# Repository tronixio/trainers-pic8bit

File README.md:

# PIC 8-Bit Trainers Boards.

## Schematics.

- [**Nano** Trainer.](https://github.com/tronixio/trainers-pic8bit/blob/main/Kicad/nano/extras/schematic.pdf)
- [TODO - Micro Trainer.](https://github.com/tronixio/trainers-pic8bit/blob/main/Kicad/micro/extras/schematic.pdf)
- [**Mini** Trainer.](https://github.com/tronixio/trainers-pic8bit/blob/main/Kicad/mini/extras/schematic.pdf)
- [**PIC 8-Bit** Trainer.](https://github.com/tronixio/trainers-pic8bit/blob/main/Kicad/trainer/extras/schematic.pdf)

## Firmwares.

- [PIC 8-Bit NANO Trainer.](https://github.com/tronixio/trainers-pic8bit/tree/main/Firmwares#pic8-bit-nano-trainer)
- [PIC 8-Bit MINI Trainer.](https://github.com/tronixio/trainers-pic8bit/tree/main/Firmwares#pic8-bit-mini-trainer)
- [PIC 8-Bit Trainer.](https://github.com/tronixio/trainers-pic8bit/tree/main/Firmwares#pic8-bit-trainer)

## Hats & Modules.

- [Trainer Hats](https://github.com/tronixio/modules)
- [Trainer Modules (GPIO/UART/I2C/SPI)](https://github.com/tronixio/modules)

## NANO Trainer Top.

## NANO Trainer Bottom.

## MINI Trainer Top.

## MINI Trainer Bottom.

## PIC 8-Bit Trainer Top.

## PIC 8-Bit Trainer Bottom.

## Notes.

- DRAFT : Prototype OK, last check schematic, PCB & code can be modify.
- TODO : Work in progress, prototype was not good, hardware, PCB and code can be rework.

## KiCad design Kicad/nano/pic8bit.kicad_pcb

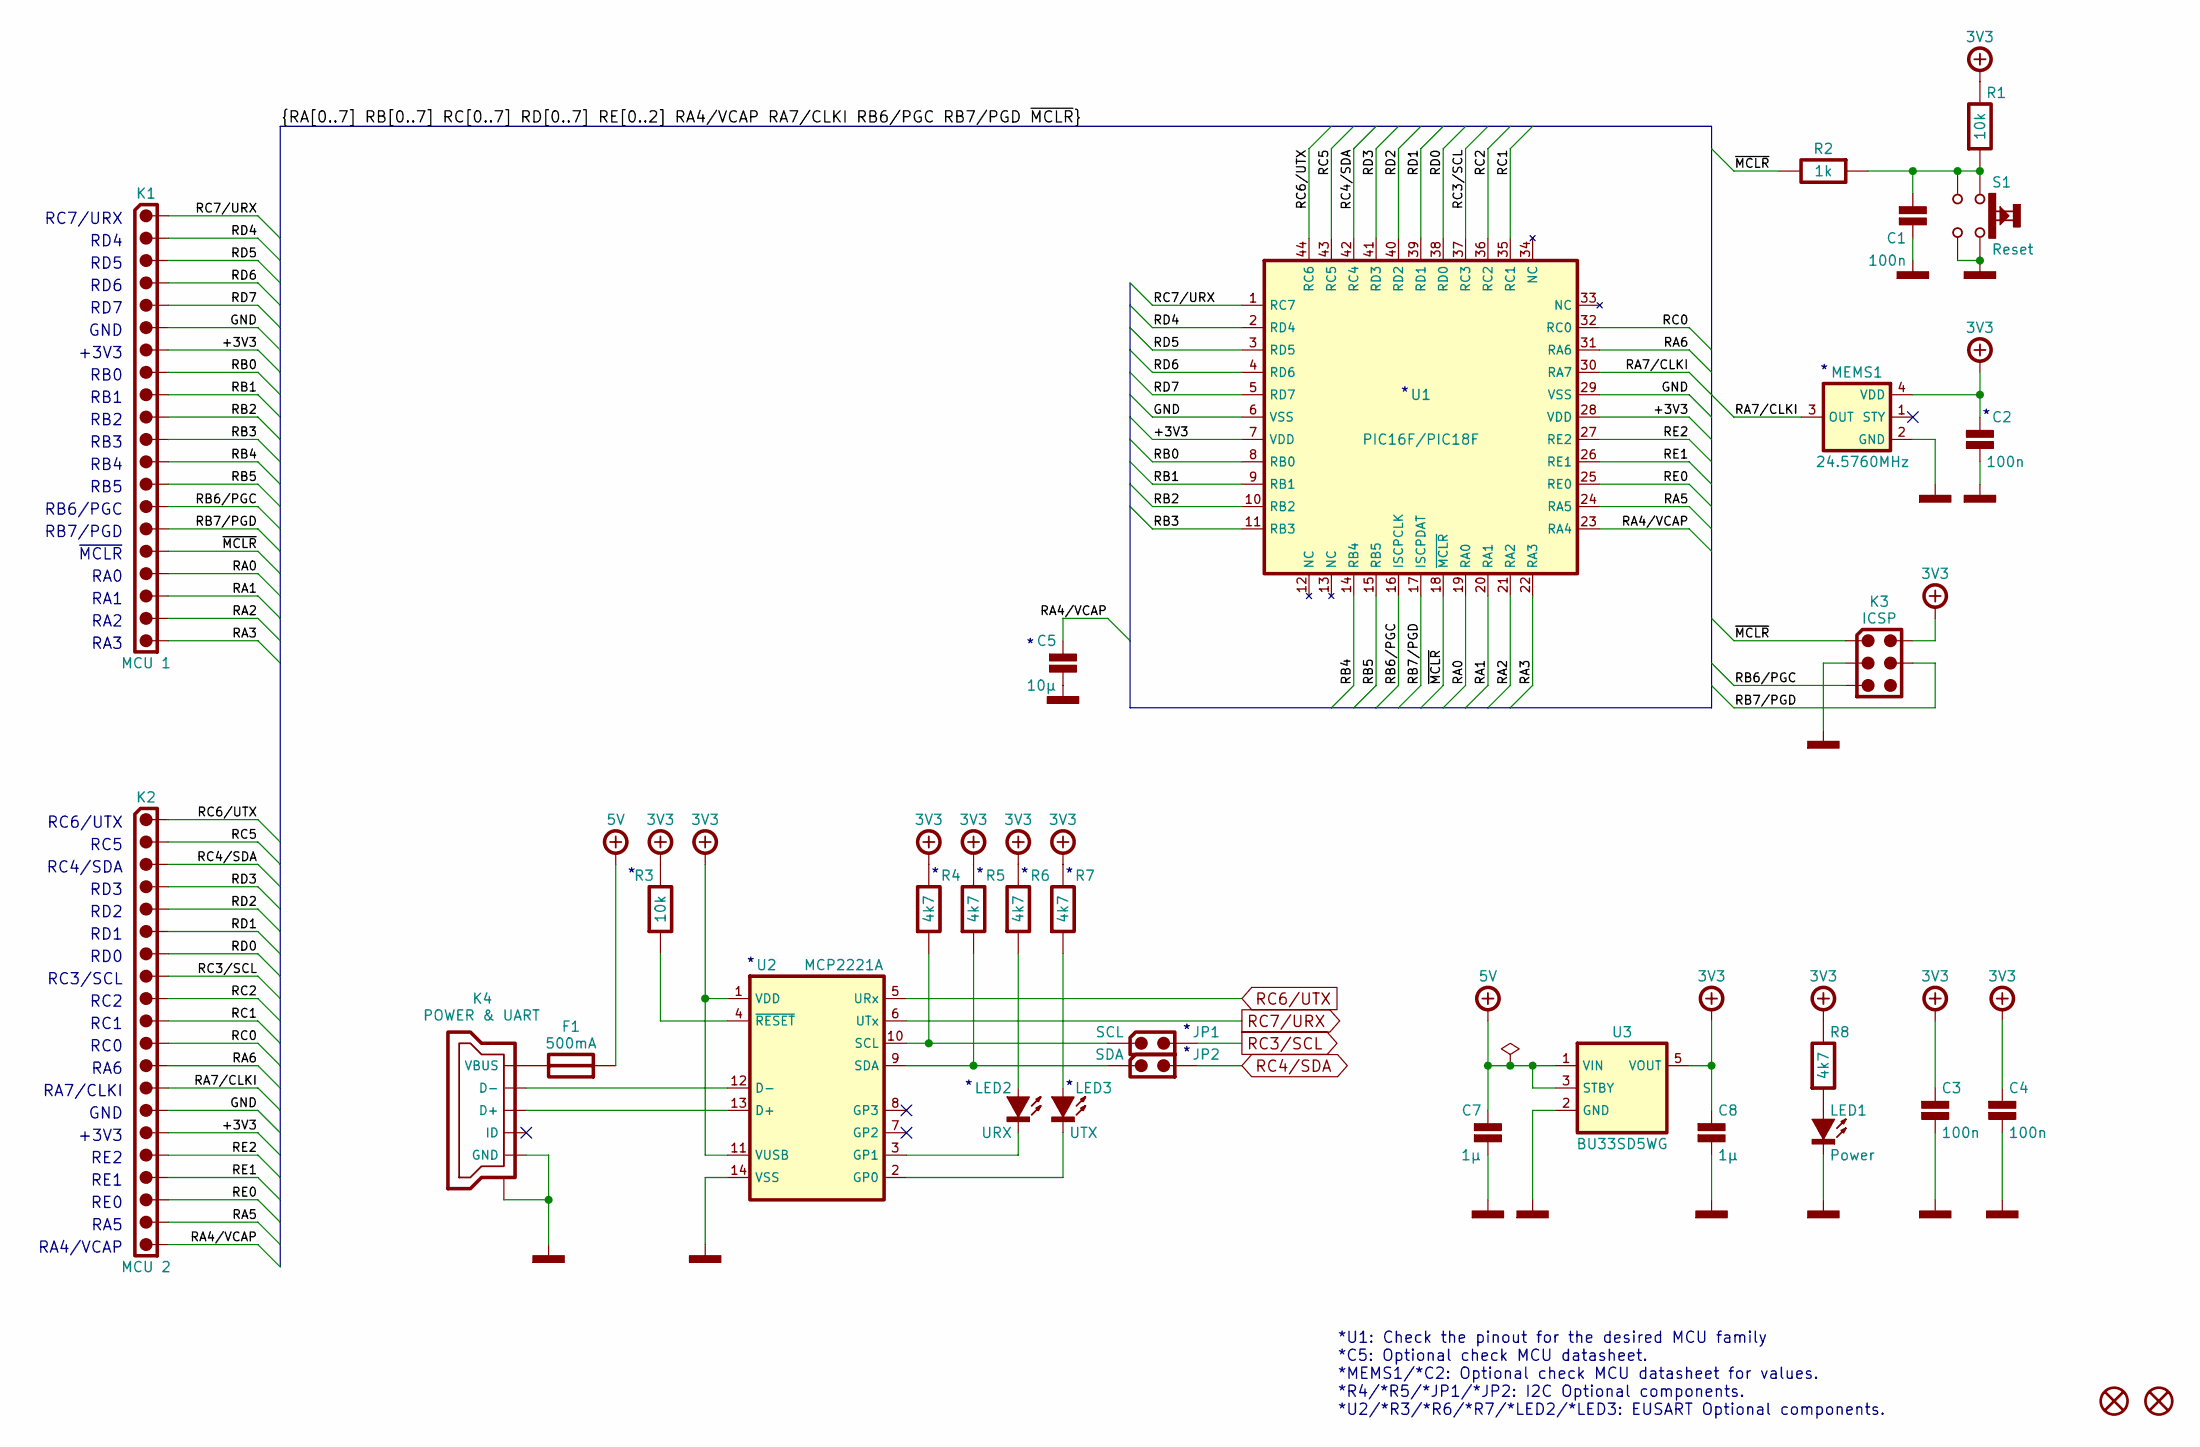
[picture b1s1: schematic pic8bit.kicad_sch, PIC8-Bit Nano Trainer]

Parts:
C1, C2, C3, C4: 100n; CAPACITOR-SMD-0805; Voltage 50V; Tolerance 5%; Mouser 80-C0805C104J5
C5: 10µ; CAPACITOR-SMD-0805; Voltage 25V; Tolerance 10%; Mouser 81-GRM21BZ71E106
C7, C8: 1µ; CAPACITOR-SMD-0805; Voltage 50V; Tolerance 10%; Mouser 187-CL21B105KBFNNNE
F1: 500mA; FUSE-SMD-0805; Mouser 652-MF-PSMF050X-2
H1, H2: HARWIN-JUMPER-0200-03MM-BLACK; HARWIN-M22-190-19X; Mouser 855-M22-19000
JP1: SCL; HARWIN-M22-25102xx; Mouser 855-M22-25102
JP2: SDA; HARWIN-M22-25102xx; Mouser 855-M22-25102
K1: MCU 1; SAMTEC-TSW-120-22-T-S; Mouser 200-TSW12022TS
K2: MCU 2; SAMTEC-TSW-120-22-T-S; Mouser 200-TSW12022TS
K3: ICSP; HARWIN-M20-998034x; Mouser 855-M20-998034
K4: POWER & UART; USB-TYPE-B-MICRO-TH; Mouser 649-10118193-0001LF
LED1: Power; LED-SMD-0805; Mouser 604-APT2012LVBCD
LED2: URX; LED-SMD-0805; Mouser 604-APT2012LVBCD
LED3: UTX; LED-SMD-0805; Mouser 604-APT2012LVBCD
MEMS1: 24.5760MHz; CDFN-3225; Mouser 998-1001CI2-024.5760
R1, R3: 10k; RESISTOR-SMD-0805; Tolerance 5%; Mouser 660-RK73B2ATTDD103J
R2: 1k; RESISTOR-SMD-0805; Tolerance 5%; Mouser 660-RK73B2ATTDD102J
R4, R5, R6, R7, R8: 4k7; RESISTOR-SMD-0805; Tolerance 5%; Mouser 660-RK73B2ATTDD472J
S1: Reset; ALPS-SKRPAC; Mouser 688-SKRPACE010
U1: PIC16F/PIC18F; TQFP-44; Mouser 579-PIC16F1779-I/PT
U2: MCP2221A; TSSOP-14; Mouser 579-MCP2221A-I/ST
U3: BU33SD5WG; SOT-23-5; Mouser 755-BU33SD5WG-TR

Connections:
+3V3: C2.1, C3.1, C4.1, C8.1, K1.7, K2.15, K3.2 (VCC), MEMS1.4 (VDD), R1.1, R3.1, R4.1, R5.1, R6.1, R7.1, R8.1, U1.7 (VDD), U1.28 (VDD), U2.1 (VDD), U2.11 (VUSB), U3.5 (VOUT)
/RA0: K1.17, U1.19 (RA0)
/RA1: K1.18, U1.20 (RA1)
/RA2: K1.19, U1.21 (RA2)
/RA3: K1.20, U1.22 (RA3)
/RA4/VCAP: C5.1, K2.20, U1.23 (RA4)
/RA5: K2.19, U1.24 (RA5)
/RA6: K2.12, U1.31 (RA6)
/RA7/CLKI: K2.13, MEMS1.3 (OUT), U1.30 (RA7)
/RB0: K1.8, U1.8 (RB0)
/RB1: K1.9, U1.9 (RB1)
/RB2: K1.10, U1.10 (RB2)
/RB3: K1.11, U1.11 (RB3)
/RB4: K1.12, U1.14 (RB4)
/RB5: K1.13, U1.15 (RB5)
/RB6/PGC: K1.14, K3.5 (ICSPCLK), U1.16 (ISCPCLK)
/RB7/PGD: K1.15, K3.4 (ICSPDAT), U1.17 (ISCPDAT)
/RC0: K2.11, U1.32 (RC0)
/RC1: K2.10, U1.35 (RC1)
/RC2: K2.9, U1.36 (RC2)
/RC5: K2.2, U1.43 (RC5)
/RD0: K2.7, U1.38 (RD0)
/RD1: K2.6, U1.39 (RD1)
/RD2: K2.5, U1.40 (RD2)
/RD3: K2.4, U1.41 (RD3)
/RD4: K1.2, U1.2 (RD4)
/RD5: K1.3, U1.3 (RD5)
/RD6: K1.4, U1.4 (RD6)
/RD7: K1.5, U1.5 (RD7)
/RE0: K2.18, U1.25 (RE0)
/RE1: K2.17, U1.26 (RE1)
/RE2: K2.16, U1.27 (RE2)
/~MCLR: K1.16, K3.1 (~MCLR), R2.1, U1.18 (~MCLR)
GND: C1.2, C2.2, C3.2, C4.2, C5.2, C7.2, C8.2, K1.6, K2.14, K3.3 (GND), K4.5 (GND), K4.SH (SHIELD), LED1.1 (C), MEMS1.2 (GND), S1.3, S1.4, U1.6 (VSS), U1.29 (VSS), U2.14 (VSS), U3.2 (GND)
unnamed: C1.1, R1.2, R2.2, S1.1, S1.2
unnamed: K4.3 (D+), U2.13 (D+)
unnamed: K4.2 (D-), U2.12 (D-)
unnamed: F1.1, K4.1 (VBUS)
unnamed: LED1.2 (A), R8.2
unnamed: LED2.2 (A), R6.2
unnamed: LED2.1 (C), U2.3 (GP1)
unnamed: LED3.2 (A), R7.2
unnamed: LED3.1 (C), U2.2 (GP0)
unnamed: JP1.1, R4.2, U2.10 (SCL)
unnamed: JP2.1, R5.2, U2.9 (SDA)
unnamed: R3.2, U2.4 (~RESET)
POWER-+5V: C7.1, F1.2, U3.1 (VIN), U3.3 (STBY)
RC3/SCL: JP1.2, K2.8, U1.37 (RC3)
RC4/SDA: JP2.2, K2.3, U1.42 (RC4)
RC6/UTX: K2.1, U1.44 (RC6), U2.5 (URx)
RC7/URX: K1.1, U1.1 (RC7), U2.6 (UTx)

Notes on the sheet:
RD7
RA7/CLKI
RB0
RD5
RC6/UTX
GND
RB4
RA4/VCAP
RB1
RE0
RC3/SCL
~{MCLR}
RB2
+3V3
RE1
RB5
RA6
RD1
RD3
RD6
RB3
RA3
*U1: Check the pinout for the desired MCU family *C5: Optional check MCU datasheet. *MEMS1/*C2: Optional check MCU datasheet for values. *R4/*R5/*JP1/*JP2: I2C Optional components. *U2/*R3/*R6/*R7/*LED2/*LED3: EUSART Optional components.
RE2
RA1
RB7/PGD
RA2
RC5
RC0
RC4/SDA
RA0
RA5
RB6/PGC
RD2
RD0
RC2
RC7/URX
RC1
RD4

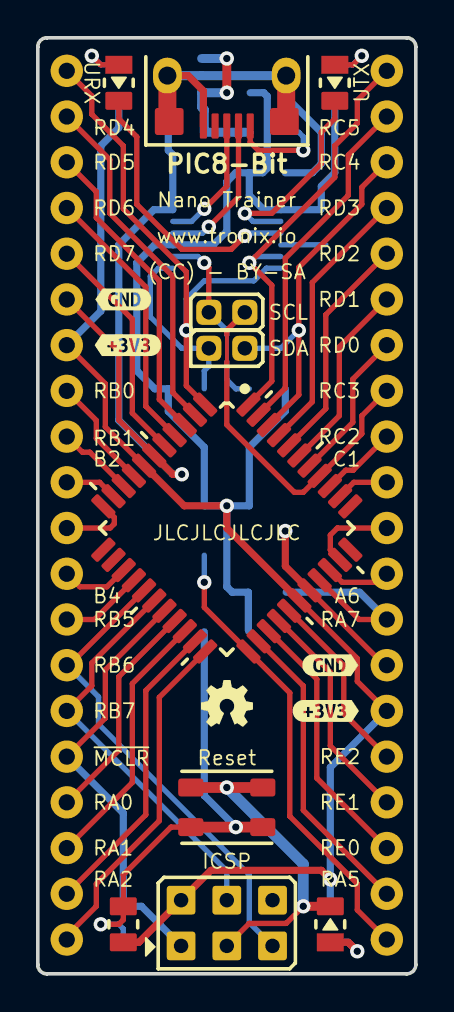
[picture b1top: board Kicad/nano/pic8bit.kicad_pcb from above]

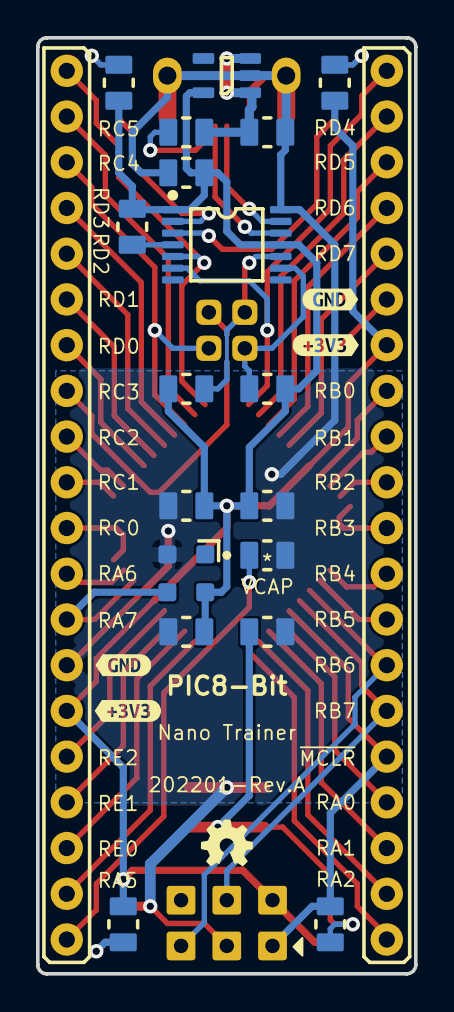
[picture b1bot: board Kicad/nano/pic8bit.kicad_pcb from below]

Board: 2 copper layers, 21.0 x 52.0 mm, 42 parts (25 on the bottom side), 51 nets.

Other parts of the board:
GB: LOGO; OSHW-3MM
GT: LOGO; OSHW-3MM
kibuzzard-65F5BE0B: G***; kibuzzard-65F5BE0B
kibuzzard-65F5BE2C: G***; kibuzzard-65F5BE2C
kibuzzard-65F5BE3D: G***; kibuzzard-65F5BE3D
kibuzzard-65F5BE5D: G***; kibuzzard-65F5BE5D
kibuzzard-65F5BE6D: G***; kibuzzard-65F5BE6D
kibuzzard-65F5BE7D: G***; kibuzzard-65F5BE7D
kibuzzard-65F5BE8C: G***; kibuzzard-65F5BE8C
kibuzzard-65F5BE49: G***; kibuzzard-65F5BE49

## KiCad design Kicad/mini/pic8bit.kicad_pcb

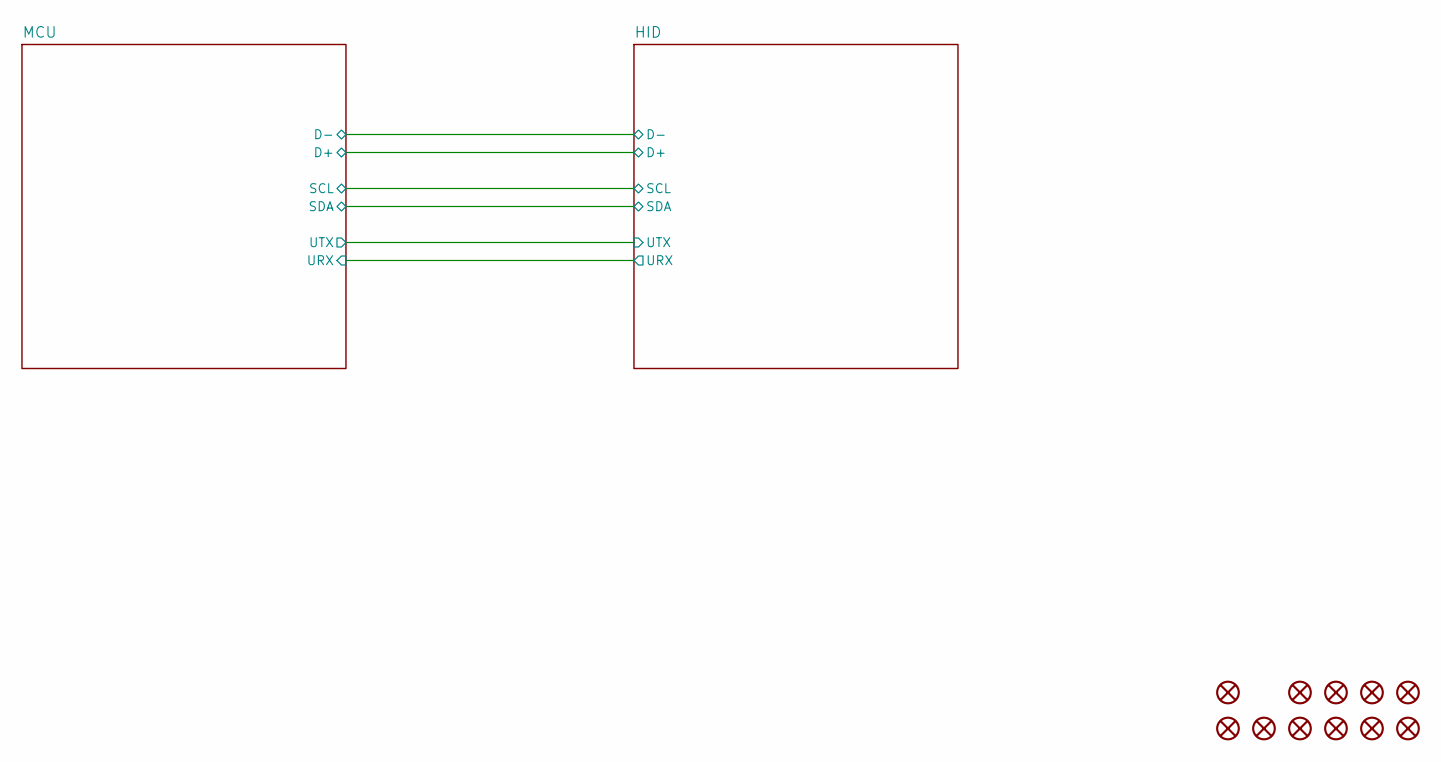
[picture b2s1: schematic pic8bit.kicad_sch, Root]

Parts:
H101, H102, H103, H104: KEYSTONE-9055; Mouser 534-9055
JP101, JP102, JP103, JP104, JP105, JP106: HARWIN-JUMPER-0254-06MM-BLACK; HARWIN-M20-7580-7583; Mouser 855-M7582
K101: PE-450-4X6X-BLACK; PE-450-4X6X; Mouser 450-476

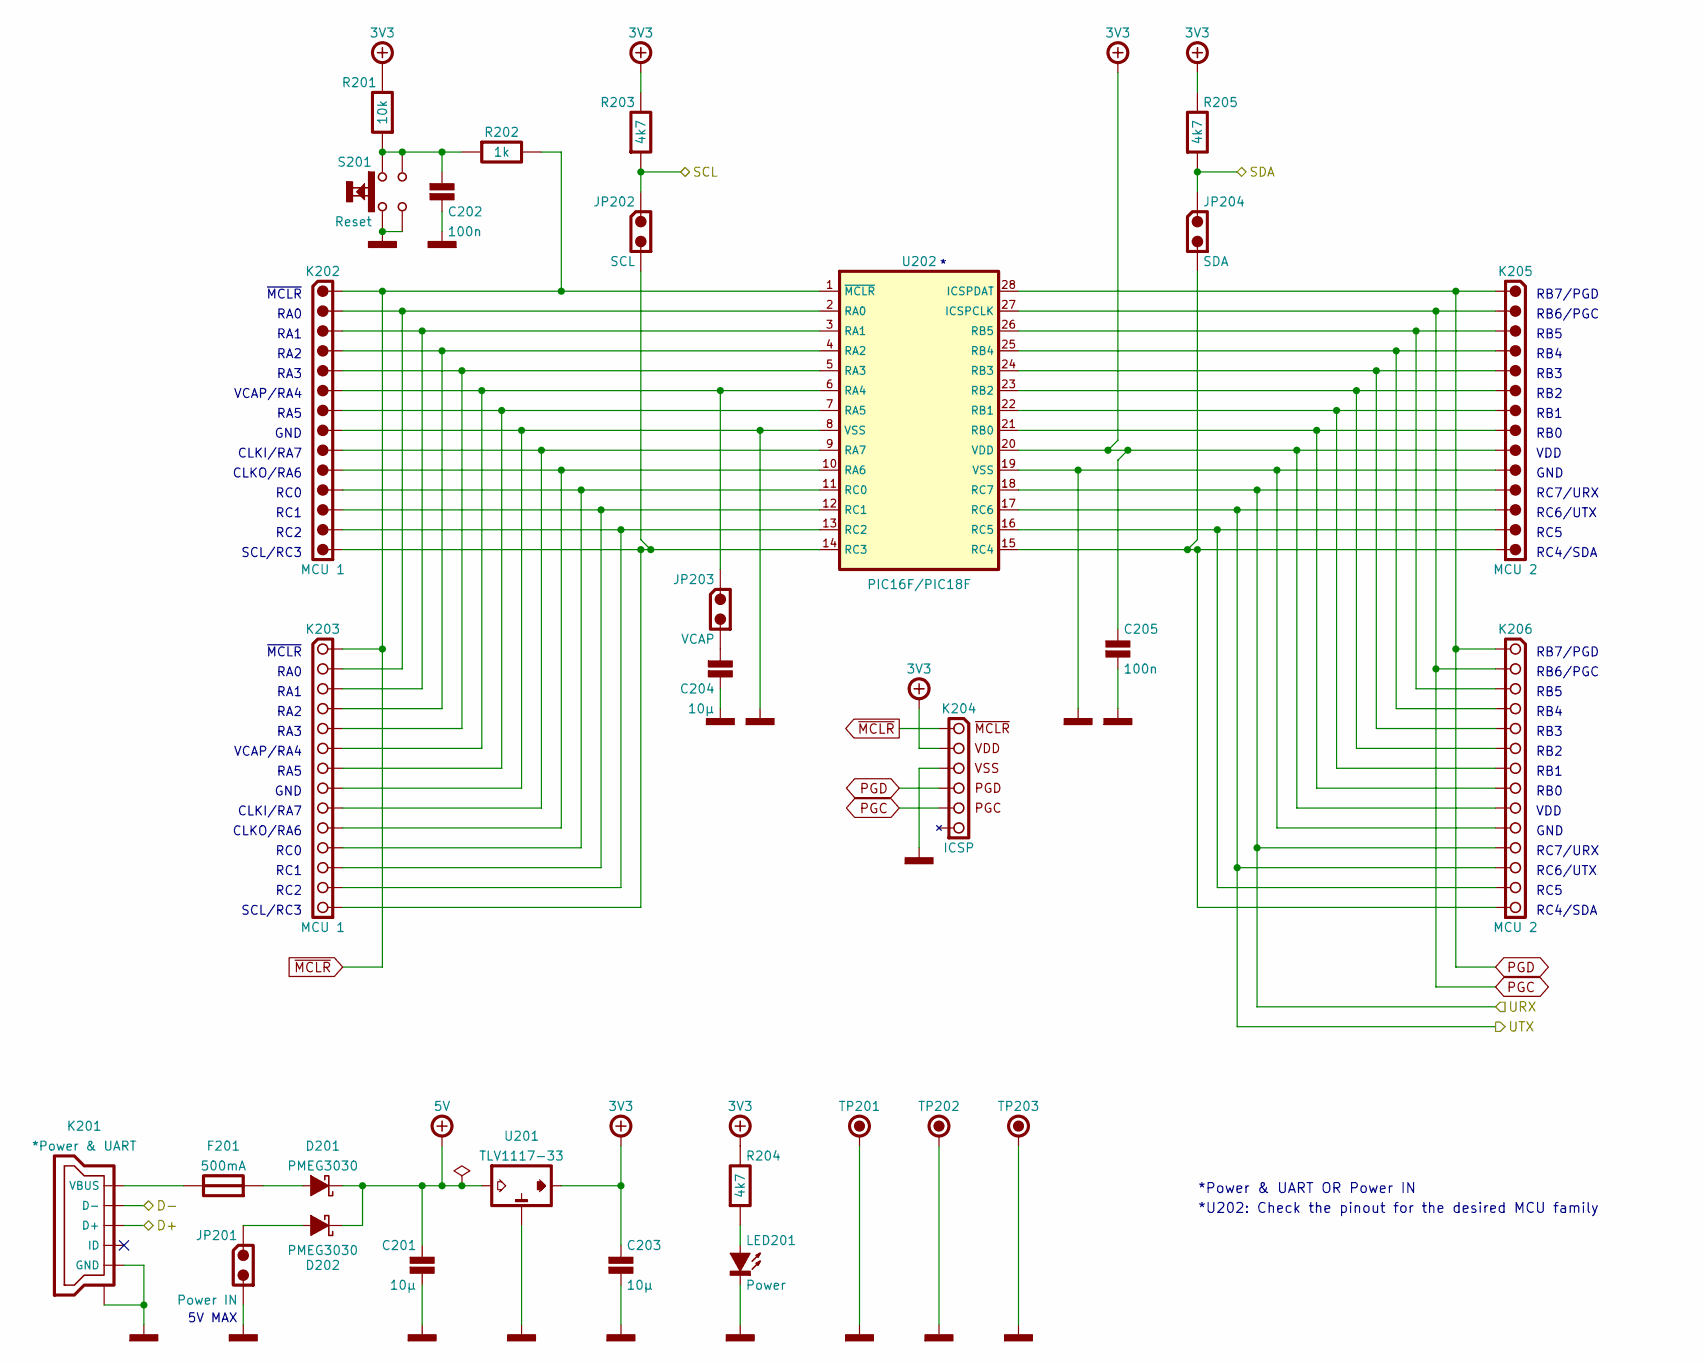
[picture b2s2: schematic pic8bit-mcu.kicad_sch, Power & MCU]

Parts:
C201, C203, C204: 10µ; CAPACITOR-SMD-1206; Tolerance 5%; Voltage 25V; Mouser 80-C1206C106J3R
C202, C205: 100n; CAPACITOR-SMD-1206; Voltage 50V; Tolerance 5%; Mouser 80-C1206C104J5R
D201, D202: PMEG3030; SOD-128; Part Marking A5; Mouser 771-PMEG3030EP115
F201: 500mA; FUSE-SMD-1206; Mouser 652-MF-NSMF050-2
JP201: Power IN; HARWIN-M20-999024x; Mouser 855-M20-999024
JP202: SCL; HARWIN-M20-999024x; Mouser 855-M20-999024
JP203: VCAP; HARWIN-M20-999024x; Mouser 855-M20-999024
JP204: SDA; HARWIN-M20-999024x; Mouser 855-M20-999024
K201: *Power & UART; USB-TYPE-B-MICRO-TH; Mouser 649-10118193-0001LF
K202: MCU 1; HARWIN-M20-999144x; Mouser 855-M20-999144
K203: MCU 1; HARWIN-M20-782144x; Mouser 855-M20-782144
K204: ICSP; SAMTEC-SSW-106-02-T-S-RA; Mouser 200-SSW10602TSRA
K205: MCU 2; HARWIN-M20-999144x; Mouser 855-M20-999144
K206: MCU 2; HARWIN-M20-782144x; Mouser 855-M20-782144
LED201: Power; LED-SMD-1206; Mouser 604-APT3216LVBCD
R201: 10k; RESISTOR-SMD-1206; Tolerance 5%; Mouser 660-RK73B2BTTDD103J
R202: 1k; RESISTOR-SMD-1206; Tolerance 5%; Mouser 660-RK73B2BTTDD102J
R203, R204, R205: 4k7; RESISTOR-SMD-1206; Tolerance 5%; Mouser 660-RK73B2BTTDD472J
S201: Reset; ALPS-SKRPAC; Mouser 688-SKRPACE010
TP201, TP202: KEYSTONE-5006; Mouser 534-5006
TP203: KEYSTONE-2000-3; Mouser 534-2000-3
U201: TLV1117-33; SOT-223-3-TABPIN2; Mouser 595-TLV1117-33CDC
U202: PIC16F/PIC18F; DIP-28-W762; Mouser 579-PIC16F1778-I/SP

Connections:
/HID/D+: K201.3 (D+); also elsewhere on the board
/HID/D-: K201.2 (D-); also elsewhere on the board
/HID/SCL: JP202.1, R203.2; also elsewhere on the board
/HID/SDA: JP204.1, R205.2; also elsewhere on the board
/HID/URX: K205.11, K206.11, U202.18 (RC7); also elsewhere on the board
/HID/UTX: K205.12, K206.12, U202.17 (RC6); also elsewhere on the board
unnamed: C202.1, R201.2, R202.2, S201.1, S201.2
unnamed: C204.1, JP203.2
unnamed: D201.2 (A), F201.2
unnamed: D202.2 (A), JP201.1
unnamed: F201.1, K201.1 (VBUS)
unnamed: K202.2, K203.2, U202.2 (RA0)
unnamed: K202.3, K203.3, U202.3 (RA1)
unnamed: K202.4, K203.4, U202.4 (RA2)
unnamed: K202.5, K203.5, U202.5 (RA3)
unnamed: JP203.1, K202.6, K203.6, U202.6 (RA4)
unnamed: K202.7, K203.7, U202.7 (RA5)
unnamed: K202.9, K203.9, U202.9 (RA7)
unnamed: K202.10, K203.10, U202.10 (RA6)
unnamed: K202.11, K203.11, U202.11 (RC0)
unnamed: K202.12, K203.12, U202.12 (RC1)
unnamed: K202.13, K203.13, U202.13 (RC2)
unnamed: JP202.2, K202.14, K203.14, U202.14 (RC3)
unnamed: K205.3, K206.3, U202.26 (RB5)
unnamed: K205.4, K206.4, U202.25 (RB4)
unnamed: K205.5, K206.5, U202.24 (RB3)
unnamed: K205.6, K206.6, U202.23 (RB2)
unnamed: K205.7, K206.7, U202.22 (RB1)
unnamed: K205.8, K206.8, U202.21 (RB0)
unnamed: K205.13, K206.13, U202.16 (RC5)
unnamed: JP204.2, K205.14, K206.14, U202.15 (RC4)
unnamed: LED201.2 (A), R204.2
PGC: K204.2 (PGC), K205.2, K206.2, U202.27 (ICSPCLK)
PGD: K204.3 (PGD), K205.1, K206.1, U202.28 (ICSPDAT)
POWER-+3V3: C203.1, C205.1, K204.5 (VCC), K205.9, K206.9, R201.1, R203.1, R204.1, R205.1, U201.2 (VOUT), U202.20 (VDD); also elsewhere on the board
POWER-+5V: C201.1, D201.1 (C), D202.1 (C), U201.3 (VIN); also elsewhere on the board
POWER-GND: C201.2, C202.2, C203.2, C204.2, C205.2, JP201.2, K201.5 (GND), K201.SH (SHIELD), K202.8, K203.8, K204.4 (GND), K205.10, K206.10, LED201.1 (C), S201.3, S201.4, TP201.1, TP202.1, TP203.1, U201.1 (GND), U202.8 (VSS), U202.19 (VSS); also elsewhere on the board
~MCLR: K202.1, K203.1, K204.6 (~MCLR), R202.1, U202.1 (~MCLR)

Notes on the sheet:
RC6/UTX
*U202: Check the pinout for the desired MCU family
GND
RB3
~{MCLR}
VCAP/RA4
*Power & UART OR Power IN
CLKI/RA7
RC5
RB6/PGC
RA2
VDD
RA3
RC0
RA0
RC1
RB7/PGD
RB5
RB2
RA5
RB1
RA1
CLKO/RA6
SCL/RC3
RB4
RC7/URX
RB0
5V MAX
RC4/SDA
RC2

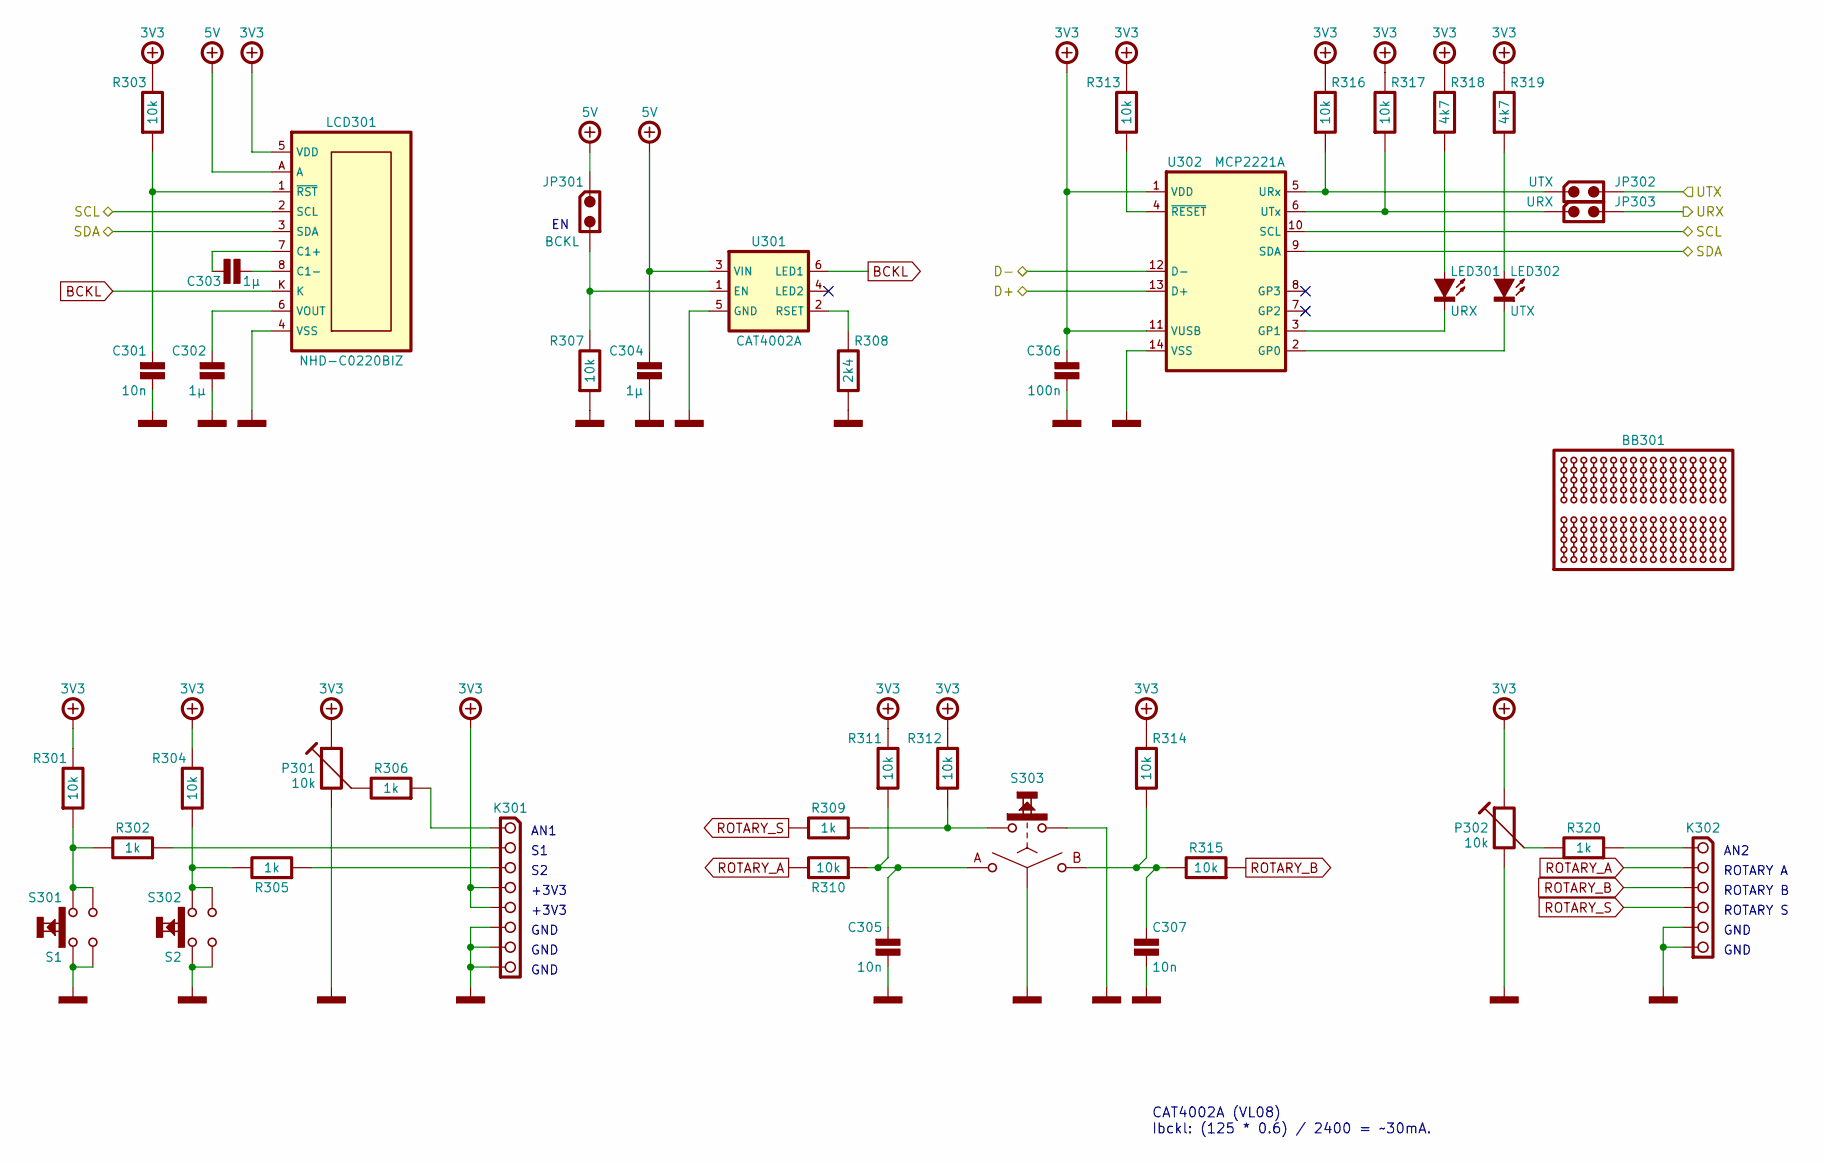
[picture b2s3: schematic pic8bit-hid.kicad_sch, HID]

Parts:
BB301: BREADBOARD-170; Mouser 854-BB170
C301, C305, C307: 10n; CAPACITOR-SMD-1206; Voltage 100V; Tolerance 5%; Mouser 80-C1206C103J1R
C302, C303, C304: 1µ; CAPACITOR-SMD-1206; Voltage 16V; Tolerance 10%; Mouser 80-C1206C105K4R
C306: 100n; CAPACITOR-SMD-1206; Voltage 50V; Tolerance 5%; Mouser 80-C1206C104J5R
JP301: BCKL; HARWIN-M20-999024x; Mouser 855-M20-999024
JP302: UTX; HARWIN-M20-999024x; Mouser 855-M20-999024
JP303: URX; HARWIN-M20-999024x; Mouser 855-M20-999024
K301: HARWIN-254-F-1X08-VERTICAL; HARWIN-M20-782084x; Mouser 855-M20-782084
K302: HARWIN-254-F-1X06-VERTICAL; HARWIN-M20-782064x; Mouser 855-M20-782064
LCD301: NHD-C0220BIZ; Mouser 763-C0220BIZ-FSW-FBW
LED301: URX; LED-SMD-1206; Mouser 604-APT3216LVBCD
LED302: UTX; LED-SMD-1206; Mouser 604-APT3216LVBCD
P301, P302: 10k; PIHER-PT10MV; Tolerance 20%; Mouser 531-PT10MV-10K
R301, R303, R304, R307, R310, R311, R312, R313, R314, R315, R316, R317: 10k; RESISTOR-SMD-1206; Tolerance 5%; Mouser 660-RK73B2BTTDD103J
R302, R305, R306, R309, R320: 1k; RESISTOR-SMD-1206; Tolerance 5%; Mouser 660-RK73B2BTTDD102J
R308: 2k4; RESISTOR-SMD-1206; Tolerance 5%; Mouser 660-RK73B2BTTDD242J
R318, R319: 4k7; RESISTOR-SMD-1206; Tolerance 5%; Mouser 660-RK73B2BTTDD472J
S301: S1; CK-KSA-TH; Mouser 611-KSA0M911LFT
S302: S2; CK-KSA-TH; Mouser 611-KSA0M911LFT
S303: BOURNS-PEC12R-24DENTS-SWITCH; BOURNS-PEC12R-SWITCH; Mouser 652-PEC12R-4215F-S24
U301: CAT4002A; SC-70-6; Mouser 863-CAT4002ASD-GT3
U302: MCP2221A; SOIC-14; Mouser 579-MCP2221A-I/SL

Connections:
/HID/D+: U302.13 (D+); also elsewhere on the board
/HID/D-: U302.12 (D-); also elsewhere on the board
/HID/SCL: LCD301.2 (SCL), U302.10 (SCL); also elsewhere on the board
/HID/SDA: LCD301.3 (SDA), U302.9 (SDA); also elsewhere on the board
/HID/URX: JP303.2; also elsewhere on the board
/HID/UTX: JP302.2; also elsewhere on the board
BCKL: LCD301.K, U301.6 (LED1)
unnamed: K301.1, R306.2
unnamed: K301.2, R302.2
unnamed: K301.3, R305.2
unnamed: K302.1, R320.2
unnamed: C303.1, LCD301.7 (C1+)
unnamed: C303.2, LCD301.8 (C1-)
unnamed: C302.1, LCD301.6 (VOUT)
unnamed: C301.1, LCD301.1 (~RST), R303.2
unnamed: LED301.2 (A), R318.2
unnamed: LED301.1 (C), U302.3 (GP1)
unnamed: LED302.2 (A), R319.2
unnamed: LED302.1 (C), U302.2 (GP0)
unnamed: P301.2, R306.1
unnamed: P302.2, R320.1
unnamed: R301.2, R302.1, S301.3, S301.4
unnamed: R304.2, R305.1, S302.3, S302.4
unnamed: R309.2, R312.2, S303.5
unnamed: C305.1, R310.2, R311.2, S303.1 (A)
unnamed: C307.1, R314.2, R315.1, S303.3 (B)
unnamed: JP301.2, R307.1, U301.1 (EN)
unnamed: R308.1, U301.2 (RSET)
unnamed: JP302.1, R316.2, U302.5 (URx)
unnamed: JP303.1, R317.2, U302.6 (UTx)
unnamed: R313.2, U302.4 (~RESET)
POWER-+3V3: C306.1, K301.4, K301.5, LCD301.5 (VDD), P301.3, P302.3, R301.1, R303.1, R304.1, R311.1, R312.1, R313.1, R314.1, R316.1, R317.1, R318.1, R319.1, U302.1 (VDD), U302.11 (VUSB); also elsewhere on the board
POWER-+5V: C304.1, JP301.1, LCD301.A, U301.3 (VIN); also elsewhere on the board
POWER-GND: C301.2, C302.2, C304.2, C305.2, C306.2, C307.2, K301.6, K301.7, K301.8, K302.5, K302.6, LCD301.4 (VSS), P301.1, P302.1, R307.2, R308.2, S301.1, S301.2, S302.1, S302.2, S303.2 (C), S303.4, U301.5 (GND), U302.14 (VSS); also elsewhere on the board
ROTARY_A: K302.2, R310.1
ROTARY_B: K302.3, R315.2
ROTARY_S: K302.4, R309.1

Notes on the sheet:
AN1
GND
ROTARY A
ROTARY B
AN2
+3V3
CAT4002A (VL08) Ibckl: (125 * 0.6) / 2400 = ~30mA.
ROTARY S

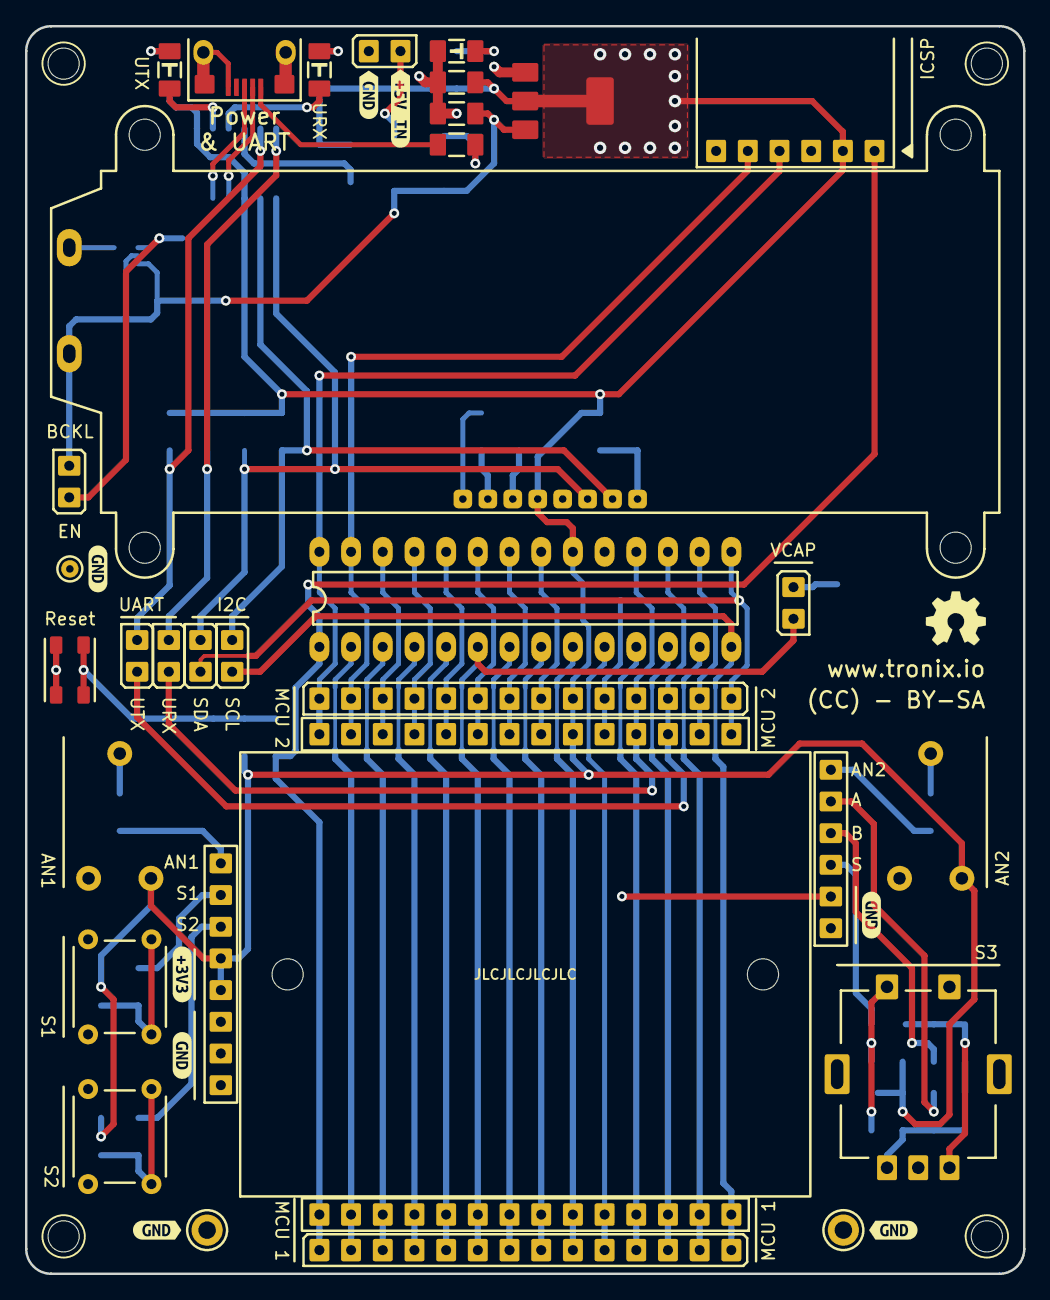
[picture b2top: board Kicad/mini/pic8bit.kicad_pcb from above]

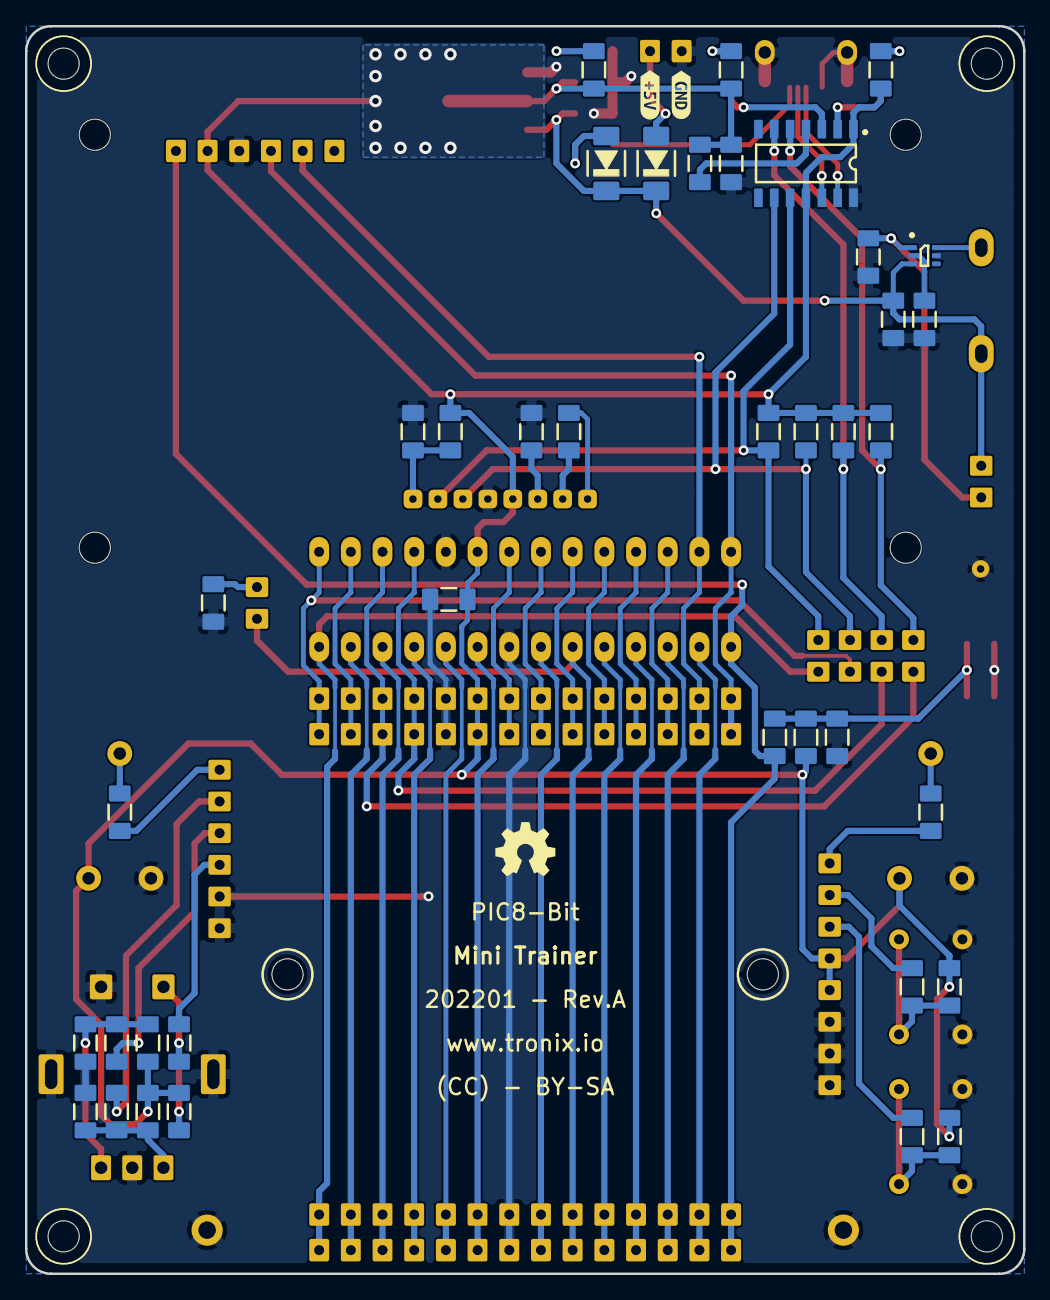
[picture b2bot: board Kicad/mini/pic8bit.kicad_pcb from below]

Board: 2 copper layers, 80.0 x 100.0 mm, 94 parts (41 on the bottom side), 66 nets.

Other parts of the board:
kibuzzard-65F5FBF2: G***; kibuzzard-65F5FBF2
kibuzzard-65F5FC1C: G***; kibuzzard-65F5FC1C
kibuzzard-65F5FC3B: G***; kibuzzard-65F5FC3B
kibuzzard-65F5FC4B: G***; kibuzzard-65F5FC4B
kibuzzard-65F5FC28: G***; kibuzzard-65F5FC28
kibuzzard-65F5FC57: G***; kibuzzard-65F5FC57
kibuzzard-65F5FC64: G***; kibuzzard-65F5FC64
kibuzzard-65F5FC73: G***; kibuzzard-65F5FC73
kibuzzard-65F5FC86: G***; kibuzzard-65F5FC86
kibuzzard-65F6B82D: G***; kibuzzard-65F6B82D
